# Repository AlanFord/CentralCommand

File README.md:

# CentralCommand
Central Command pcb for the Contextual Electronics class

The objective of this portion of the class was to design and build
a development board based on the STM32F030 MCU.  USB functionality
is provided via an FTDI FT232RQ device attached to USART2.
An 8Mhz external clock is provided by a crystal.  External headers
are provided for USART1, I2C2, SPI1, ADC, and a programming connection.
I2C1 functionality is provided via two JST SH connectors.  One user
LED is provided.  An on-board reset button will reset the mcu.

The board can be powered either by the USB connection or via an external power supply providing
between 3.75 and 6V.  The voltage regulator can provide a maximum of
250 mA at 3.3V.

**UPDATE:**  The board should be powered through the external power connection
P202 when the board is being programmed.  If the board is powered via the USB
connector during programming, the trace between the reset button, SW301, and
the FTD232RQ USB interface must be cut.  Without cutting this trace the mcu reset
that occurs during programming will simultaneously reset the FTD232RQ device,
momentarily powering down the entire board.

**UPDATE #2:**  The firmware folders and files have been restructured
and updated to support the use of the STM32CubeIDE.  To use the IDE,
simply create a workspace and import this project.

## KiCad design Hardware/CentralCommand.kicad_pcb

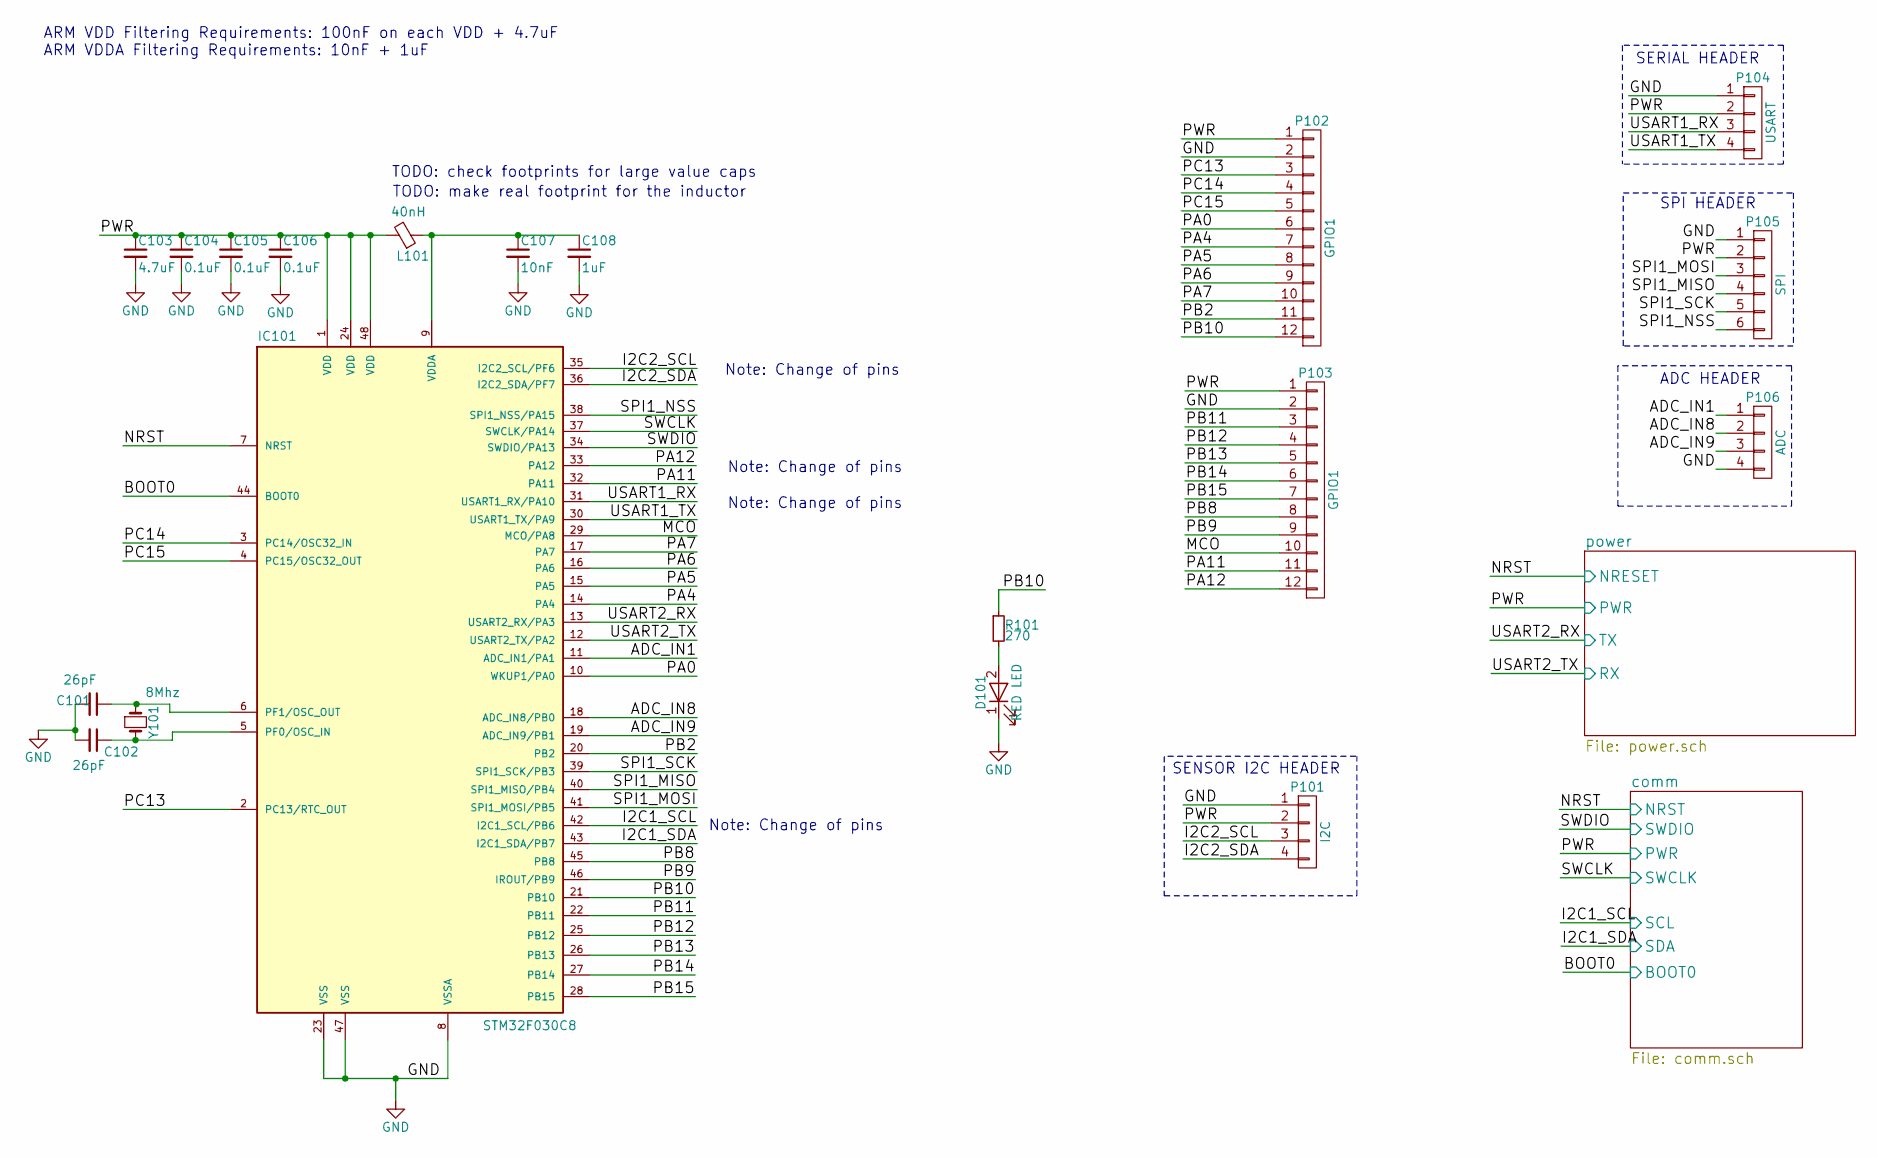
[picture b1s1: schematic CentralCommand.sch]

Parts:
C101, C102: 26pF; C_0805
C103: 4.7uF; C_0805
C104, C105, C106: 0.1uF; C_0805
C107: 10nF; C_0805
C108: 1uF; C_0805
D101: RED LED; LED_0805
IC101: STM32F030C8; LQFP-48_7x7mm_Pitch0.5mm; MPN STM32F030C8T6
L101: 40nH; C_0805; MPN MI0805K400R-10
P101: I2C; Pin_Header_Straight_1x04
P102, P103: GPIO1; Pin_Header_Straight_1x12
P104: USART; Pin_Header_Straight_1x04
P105: SPI; Pin_Header_Straight_1x06
P106: ADC; Pin_Header_Straight_1x04
R101: 270; R_0805
Y101: 8Mhz; Crystal_HC49-SD_SMD; MPN 9C-8.000MEEJ-T

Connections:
/ADC_IN1: IC101.11 (ADC_IN1/PA1), P106.1
/ADC_IN8: IC101.18 (ADC_IN8/PB0), P106.2
/ADC_IN9: IC101.19 (ADC_IN9/PB1), P106.3
/BOOT0: IC101.44 (BOOT0); also elsewhere on the board
/I2C1_SCL: IC101.42 (I2C1_SCL/PB6); also elsewhere on the board
/I2C1_SDA: IC101.43 (I2C1_SDA/PB7); also elsewhere on the board
/I2C2_SCL: IC101.35 (I2C2_SCL/PF6), P101.3
/I2C2_SDA: IC101.36 (I2C2_SDA/PF7), P101.4
/MCO: IC101.29 (MCO/PA8), P103.10
/NRST: IC101.7 (NRST); also elsewhere on the board
/PA0: IC101.10 (WKUP1/PA0), P102.6
/PA4: IC101.14 (PA4), P102.7
/PA5: IC101.15 (PA5), P102.8
/PA6: IC101.16 (PA6), P102.9
/PA7: IC101.17 (PA7), P102.10
/PA11: IC101.32 (PA11), P103.11
/PA12: IC101.33 (PA12), P103.12
/PB2: IC101.20 (PB2), P102.11
/PB8: IC101.45 (PB8), P103.8
/PB9: IC101.46 (IROUT/PB9), P103.9
/PB10: IC101.21 (PB10), P102.12, R101.1
/PB11: IC101.22 (PB11), P103.3
/PB12: IC101.25 (PB12), P103.4
/PB13: IC101.26 (PB13), P103.5
/PB14: IC101.27 (PB14), P103.6
/PB15: IC101.28 (PB15), P103.7
/PC13: IC101.2 (PC13/RTC_OUT), P102.3
/PC14: IC101.3 (PC14/OSC32_IN), P102.4
/PC15: IC101.4 (PC15/OSC32_OUT), P102.5
/PWR: C103.1, C104.1, C105.1, C106.1, IC101.1 (VDD), IC101.24 (VDD), IC101.48 (VDD), L101.2, P101.2, P102.1, P103.1, P104.2, P105.2; also elsewhere on the board
/SPI1_MISO: IC101.40 (SPI1_MISO/PB4), P105.4
/SPI1_MOSI: IC101.41 (SPI1_MOSI/PB5), P105.3
/SPI1_NSS: IC101.38 (SPI1_NSS/PA15), P105.6
/SPI1_SCK: IC101.39 (SPI1_SCK/PB3), P105.5
/SWCLK: IC101.37 (SWCLK/PA14); also elsewhere on the board
/SWDIO: IC101.34 (SWDIO/PA13); also elsewhere on the board
/USART1_RX: IC101.31 (USART1_RX/PA10), P104.3
/USART1_TX: IC101.30 (USART1_TX/PA9), P104.4
/USART2_RX: IC101.13 (USART2_RX/PA3); also elsewhere on the board
/USART2_TX: IC101.12 (USART2_TX/PA2); also elsewhere on the board
GND: C101.2, C102.2, C103.2, C104.2, C105.2, C106.2, C107.2, C108.2, D101.1 (K), IC101.8 (VSSA), IC101.23 (VSS), IC101.47 (VSS), P101.1, P102.2, P103.2, P104.1, P105.1, P106.4; also elsewhere on the board
unnamed: C101.1, IC101.6 (PF1/OSC_OUT), Y101.1
unnamed: C102.1, IC101.5 (PF0/OSC_IN), Y101.2
unnamed: C107.1, C108.1, IC101.9 (VDDA), L101.1
unnamed: D101.2 (A), R101.2

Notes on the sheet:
ARM VDD Filtering Requirements: 100nF on each VDD + 4.7uF ARM VDDA Filtering Requirements: 10nF + 1uF
SERIAL HEADER
SPI HEADER
ADC HEADER
SENSOR I2C HEADER
Note: Change of pins
TODO: make real footprint for the inductor
TODO: check footprints for large value caps

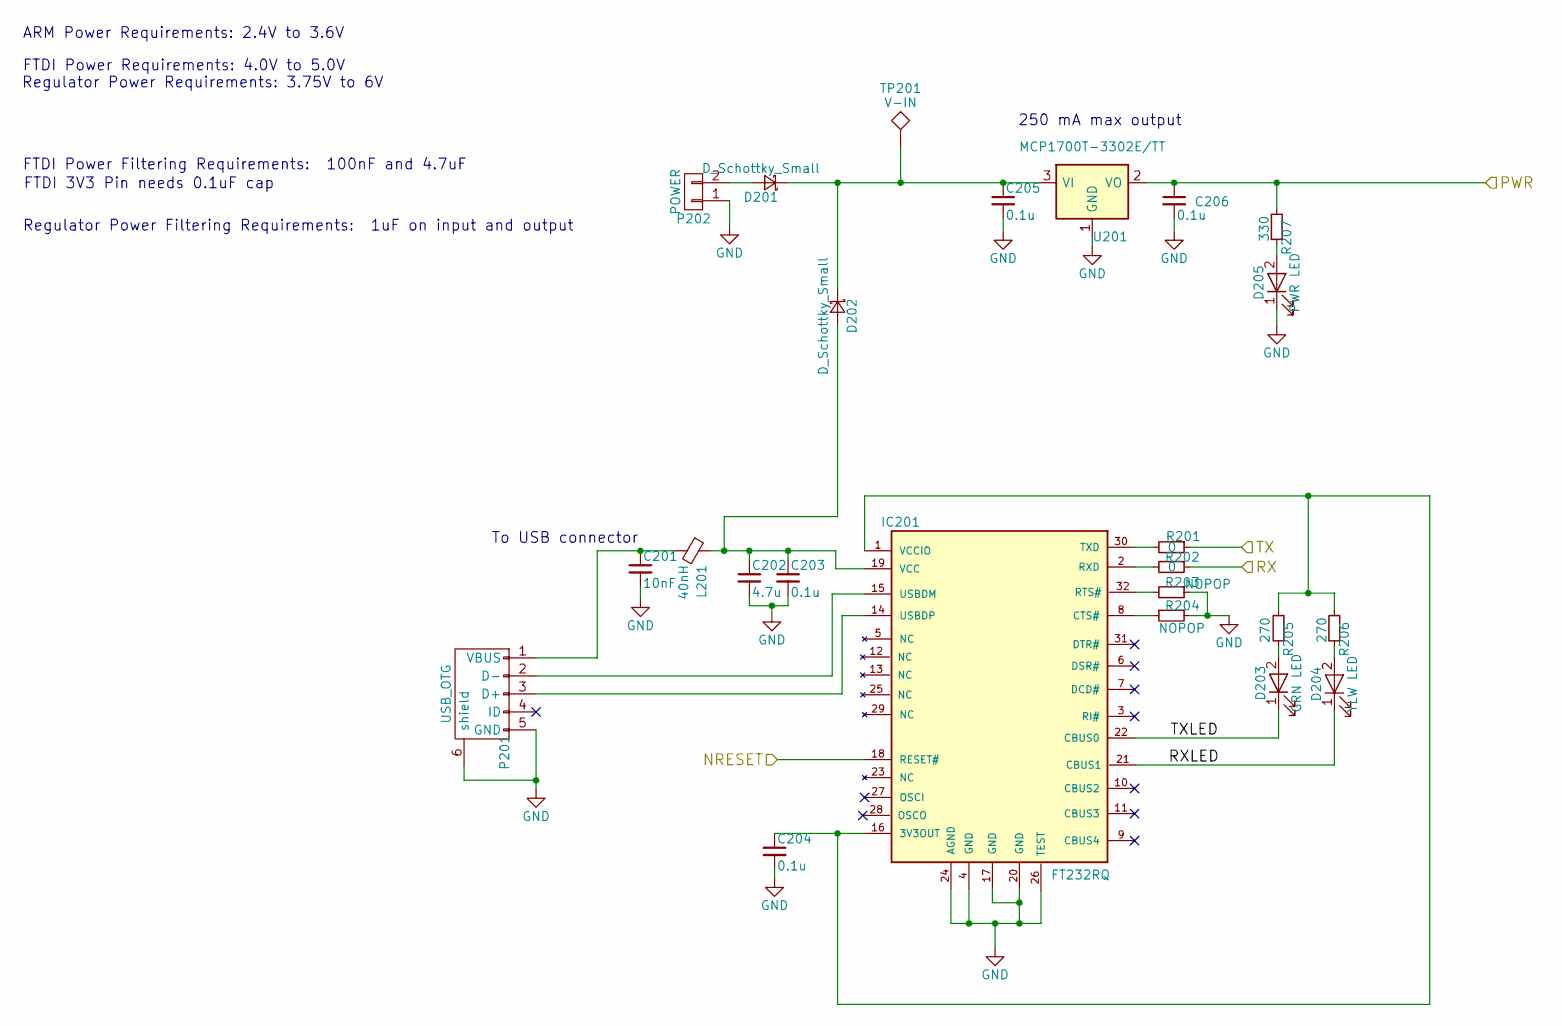
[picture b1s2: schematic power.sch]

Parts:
C201: 10nF; C_0805
C202: 4.7u; C_0805
C203, C204, C205, C206: 0.1u; C_0805
D201, D202: D_Schottky_Small; D_0805; MPN SK310A-TP
D203: GRN LED; LED_0805; MPN LTST-C171GKT
D204: YLW LED; LED_0805; MPN LTST-C171GKT
D205: PWR LED; LED_0805; MPN LTST-C171GKT
IC201: FT232RQ
L201: 40nH; C_0805; MPN MI0805K400R-10
P201: USB_OTG; 10118193; MPN 10118193-0001LF
P202: POWER; Pin_Header_Straight_1x02
R201, R202: 0; R_0805
R203, R204: NOPOP; R_0805
R205, R206: 270; R_0805
R207: 330; R_0805
TP201: V-IN; Measurement_Point_Round-SMD-Pad_Small
U201: MCP1700T-3302E/TT; SOT-23

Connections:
/NRST: IC201.18 (RESET#); also elsewhere on the board
/PWR: C206.1, R207.2, U201.2 (VO); also elsewhere on the board
/USART2_RX: R201.1; also elsewhere on the board
/USART2_TX: R202.1; also elsewhere on the board
/power/RXLED: D204.1 (K), IC201.21 (CBUS1)
/power/TXLED: D203.1 (K), IC201.22 (CBUS0)
GND: C201.2, C202.2, C203.2, C204.2, C205.2, C206.2, D205.1 (K), IC201.4 (GND), IC201.17 (GND), IC201.20 (GND), IC201.24 (AGND), IC201.26 (TEST), P201.5 (GND), P201.6 (shield), P202.1, R203.1, R204.1, U201.1 (GND); also elsewhere on the board
unnamed: C201.1, L201.2, P201.1 (VBUS)
unnamed: C202.1, C203.1, D202.2 (A), IC201.19 (VCC), L201.1
unnamed: C204.1, IC201.1 (VCCIO), IC201.16 (3V3OUT), R205.2, R206.2
unnamed: C205.1, D201.1 (K), D202.1 (K), TP201.1, U201.3 (VI)
unnamed: D201.2 (A), P202.2
unnamed: D203.2 (A), R205.1
unnamed: D204.2 (A), R206.1
unnamed: D205.2 (A), R207.1
unnamed: IC201.2 (RXD), R202.2
unnamed: IC201.8 (CTS#), R204.2
unnamed: IC201.14 (USBDP), P201.3 (D+)
unnamed: IC201.15 (USBDM), P201.2 (D-)
unnamed: IC201.30 (TXD), R201.2
unnamed: IC201.32 (RTS#), R203.2

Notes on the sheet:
ARM Power Requirements: 2.4V to 3.6V
FTDI Power Filtering Requirements: 100nF and 4.7uF
FTDI Power Requirements: 4.0V to 5.0V
Regulator Power Requirements: 3.75V to 6V
Regulator Power Filtering Requirements: 1uF on input and output
FTDI 3V3 Pin needs 0.1uF cap
To USB connector
250 mA max output

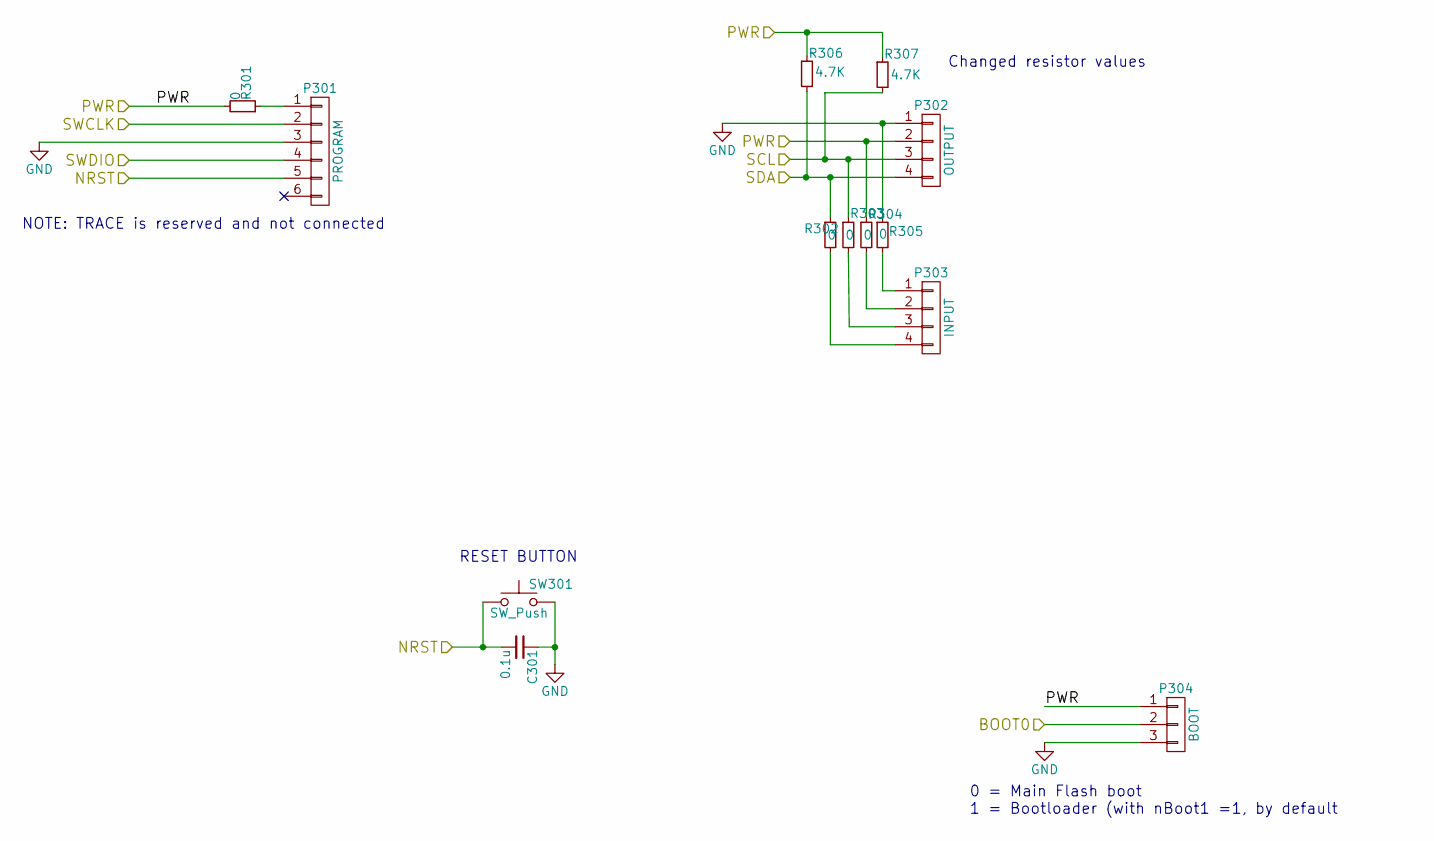
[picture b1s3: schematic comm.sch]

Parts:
C301: 0.1u; C_0805
P301: PROGRAM; Pin_Header_Straight_1x06
P302: OUTPUT; JST_SH_BM04B-SRSS-TB_04x1.00mm_Straight; MPN BM04B-SRSS-TB(LF)(SN)
P303: INPUT; JST_SH_BM04B-SRSS-TB_04x1.00mm_Straight; MPN BM04B-SRSS-TB(LF)(SN)
P304: BOOT; Pin_Header_Straight_1x03
R301, R302, R303, R304, R305: 0; R_0805
R306, R307: 4.7K; R_0805
SW301: SW_Push; TL3315; MPN TL3315NF100Q

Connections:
/BOOT0: P304.2; also elsewhere on the board
/I2C1_SCL: P302.3, R303.1, R307.2; also elsewhere on the board
/I2C1_SDA: P302.4, R302.1, R306.2; also elsewhere on the board
/NRST: C301.2, P301.5, SW301.1; also elsewhere on the board
/PWR: P302.2, P304.1, R301.2, R304.1, R306.1, R307.1; also elsewhere on the board
/SWCLK: P301.2; also elsewhere on the board
/SWDIO: P301.4; also elsewhere on the board
GND: C301.1, P301.3, P302.1, P304.3, R305.1, SW301.2; also elsewhere on the board
unnamed: P301.1, R301.1
unnamed: P303.1, R305.2
unnamed: P303.2, R304.2
unnamed: P303.3, R303.2
unnamed: P303.4, R302.2

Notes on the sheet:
NOTE: TRACE is reserved and not connected
RESET BUTTON
0 = Main Flash boot 1 = Bootloader (with nBoot1 =1, by default
Changed resistor values

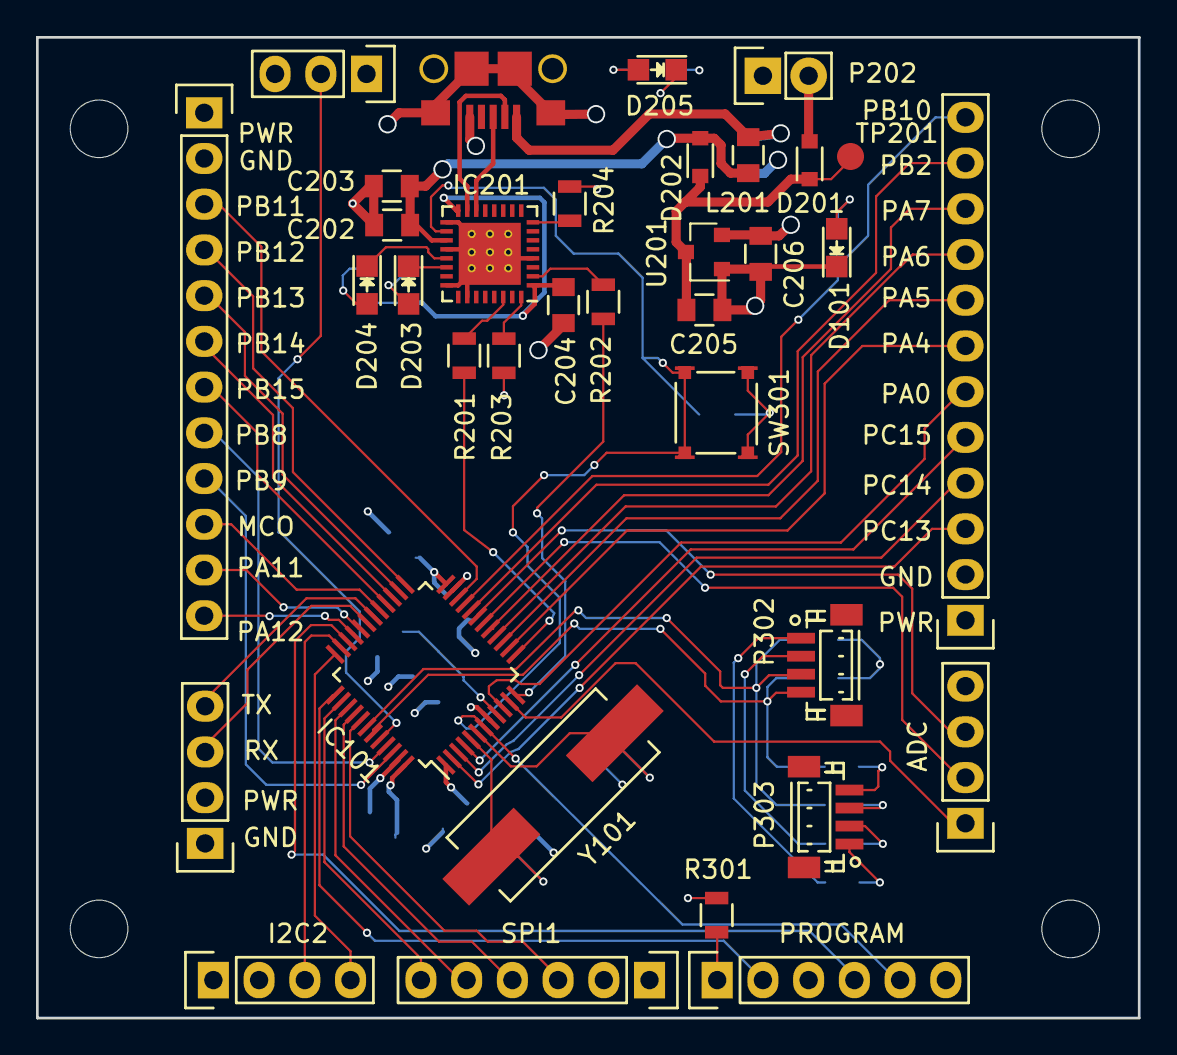
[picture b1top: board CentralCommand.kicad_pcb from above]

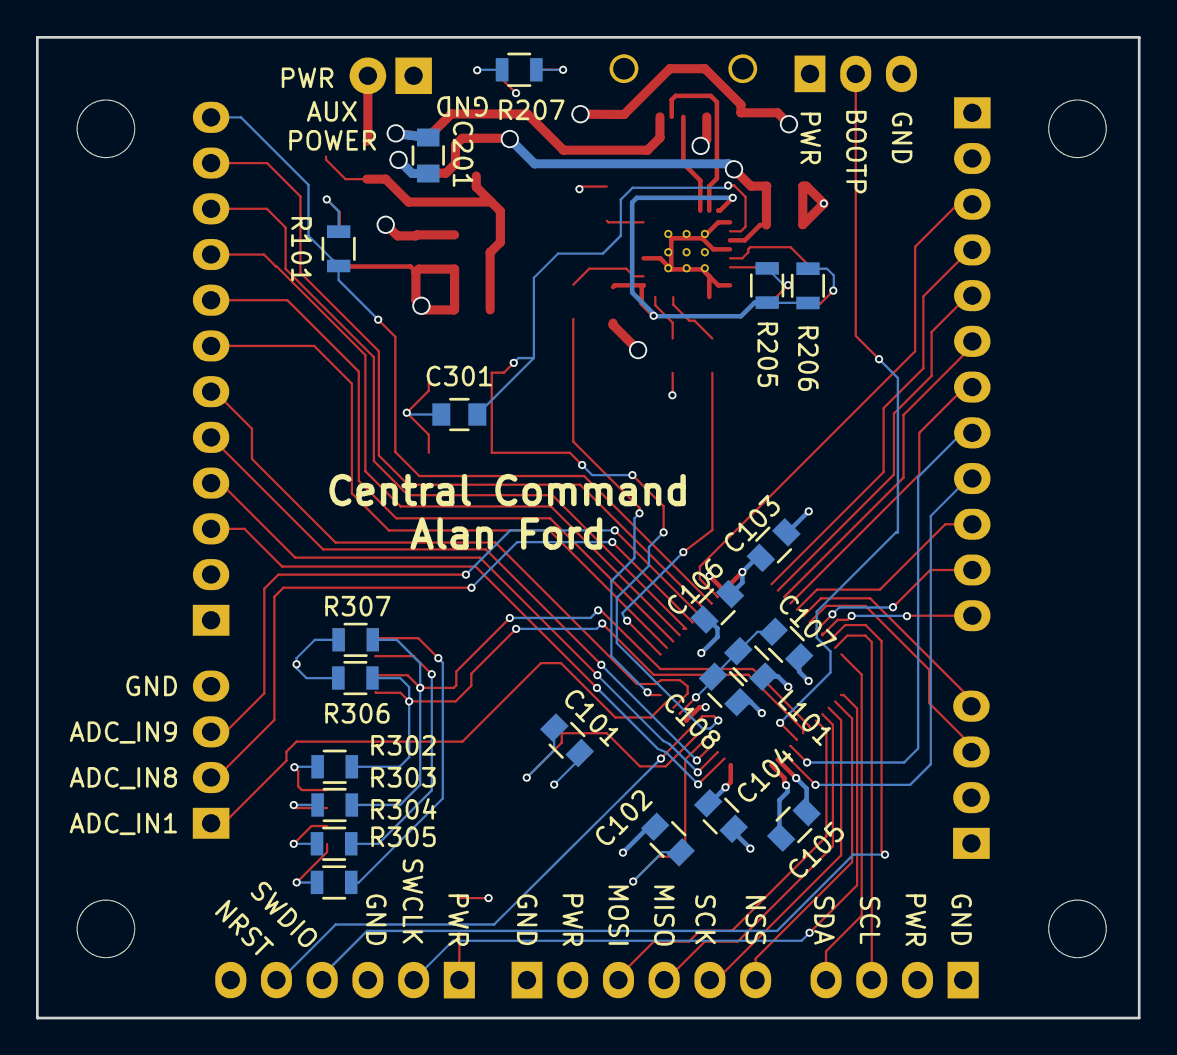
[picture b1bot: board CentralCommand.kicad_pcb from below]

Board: 4 copper layers, 61.2 x 54.5 mm, 56 parts (21 on the bottom side), 66 nets.

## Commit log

2017-03-25 initialized KiCad
2017-03-25 arranged things in folders
2017-03-25 added documentation and stm32 schematic symbol
2017-03-25 udated stm32 symbol docs
2017-03-31 updated connectors and ftdi connections
2017-04-02 reassigned pin to correct I2C1, I2C2, and USART1 connections
2017-04-02 updated STM32 symbol to reflect correct pin functions
2017-04-03 initial footprint assignments
2017-04-03 added crystal details and usb footprint
2017-04-08 changed grove connectors to jst sh and added VCC and GND to other headers
2017-04-10 fixed jst sh headers and added button footprint
2017-05-10 started board layout
2017-05-10 converted VCCIO to 3V3 and added 1x2 power and gnd
2017-05-11 swapped power and gnd on gpio headers and added blinky led
2017-05-14 more layout
2017-05-14 moved headers from power side of boards and rerouted traces
2017-05-27 continued pcb layout
2017-06-04 layout almost done
2017-06-20 relocated footprint labels
2017-06-20 labeled headers
2017-06-20 adjusted a few more labels, added mounting holes, generated gerbers
2017-06-20 created gerber archives
2021-10-01 bring everything up-to-date
2021-10-01 final up-to-date
2021-10-02 Restructure firmware to use STM32CubeIDE
    Fix a folder name
2021-10-02 update the readme
